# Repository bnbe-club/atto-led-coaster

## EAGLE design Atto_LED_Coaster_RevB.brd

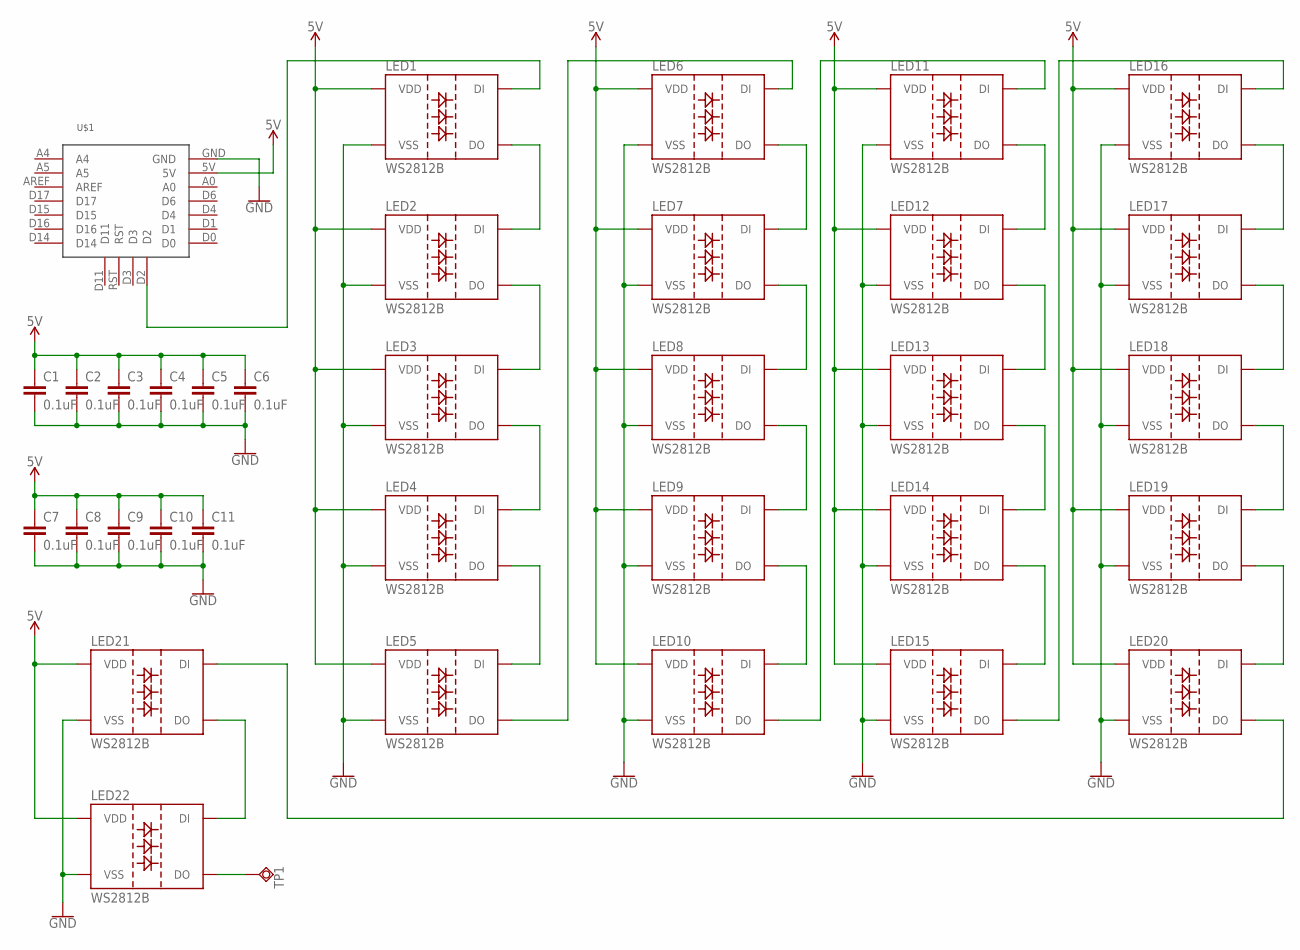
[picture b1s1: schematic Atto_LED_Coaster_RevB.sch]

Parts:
C1, C2, C3, C4, C5, C6, C7, C8, C9, C10, C11: 0.1uF; C0805
LED1, LED2, LED3, LED4, LED5, LED6, LED7, LED8, LED9, LED10, LED11, LED12, LED13, LED14, LED15, LED16, LED17, LED18, LED19, LED20, LED21, LED22: WS2812B
TP1: TPSQTP20R; TP20R
U$1: PIKSEY_ATTO

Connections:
5V: C1.1, C2.1, C3.1, C4.1, C5.1, C6.1, C7.1, C8.1, C9.1, C10.1, C11.1, LED1.3 (VDD), LED2.3 (VDD), LED3.3 (VDD), LED4.3 (VDD), LED5.3 (VDD), LED6.3 (VDD), LED7.3 (VDD), LED8.3 (VDD), LED9.3 (VDD), LED10.3 (VDD), LED11.3 (VDD), LED12.3 (VDD), LED13.3 (VDD), LED14.3 (VDD), LED15.3 (VDD), LED16.3 (VDD), LED17.3 (VDD), LED18.3 (VDD), LED19.3 (VDD), LED20.3 (VDD), LED21.3 (VDD), LED22.3 (VDD), U$1.5V
GND: C1.2, C2.2, C3.2, C4.2, C5.2, C6.2, C7.2, C8.2, C9.2, C10.2, C11.2, LED1.1 (VSS), LED2.1 (VSS), LED3.1 (VSS), LED4.1 (VSS), LED5.1 (VSS), LED6.1 (VSS), LED7.1 (VSS), LED8.1 (VSS), LED9.1 (VSS), LED10.1 (VSS), LED11.1 (VSS), LED12.1 (VSS), LED13.1 (VSS), LED14.1 (VSS), LED15.1 (VSS), LED16.1 (VSS), LED17.1 (VSS), LED18.1 (VSS), LED19.1 (VSS), LED20.1 (VSS), LED21.1 (VSS), LED22.1 (VSS), U$1.GND
unnamed: LED1.2 (DO), LED2.4 (DI)
unnamed: LED2.2 (DO), LED3.4 (DI)
unnamed: LED3.2 (DO), LED4.4 (DI)
unnamed: LED4.2 (DO), LED5.4 (DI)
unnamed: LED6.2 (DO), LED7.4 (DI)
unnamed: LED7.2 (DO), LED8.4 (DI)
unnamed: LED8.2 (DO), LED9.4 (DI)
unnamed: LED9.2 (DO), LED10.4 (DI)
unnamed: LED11.2 (DO), LED12.4 (DI)
unnamed: LED12.2 (DO), LED13.4 (DI)
unnamed: LED13.2 (DO), LED14.4 (DI)
unnamed: LED14.2 (DO), LED15.4 (DI)
unnamed: LED16.2 (DO), LED17.4 (DI)
unnamed: LED17.2 (DO), LED18.4 (DI)
unnamed: LED18.2 (DO), LED19.4 (DI)
unnamed: LED19.2 (DO), LED20.4 (DI)
unnamed: LED22.2 (DO), TP1.TP
unnamed: LED15.2 (DO), LED16.4 (DI)
unnamed: LED10.2 (DO), LED11.4 (DI)
unnamed: LED5.2 (DO), LED6.4 (DI)
unnamed: LED1.4 (DI), U$1.D2
unnamed: LED21.2 (DO), LED22.4 (DI)
unnamed: LED20.2 (DO), LED21.4 (DI)

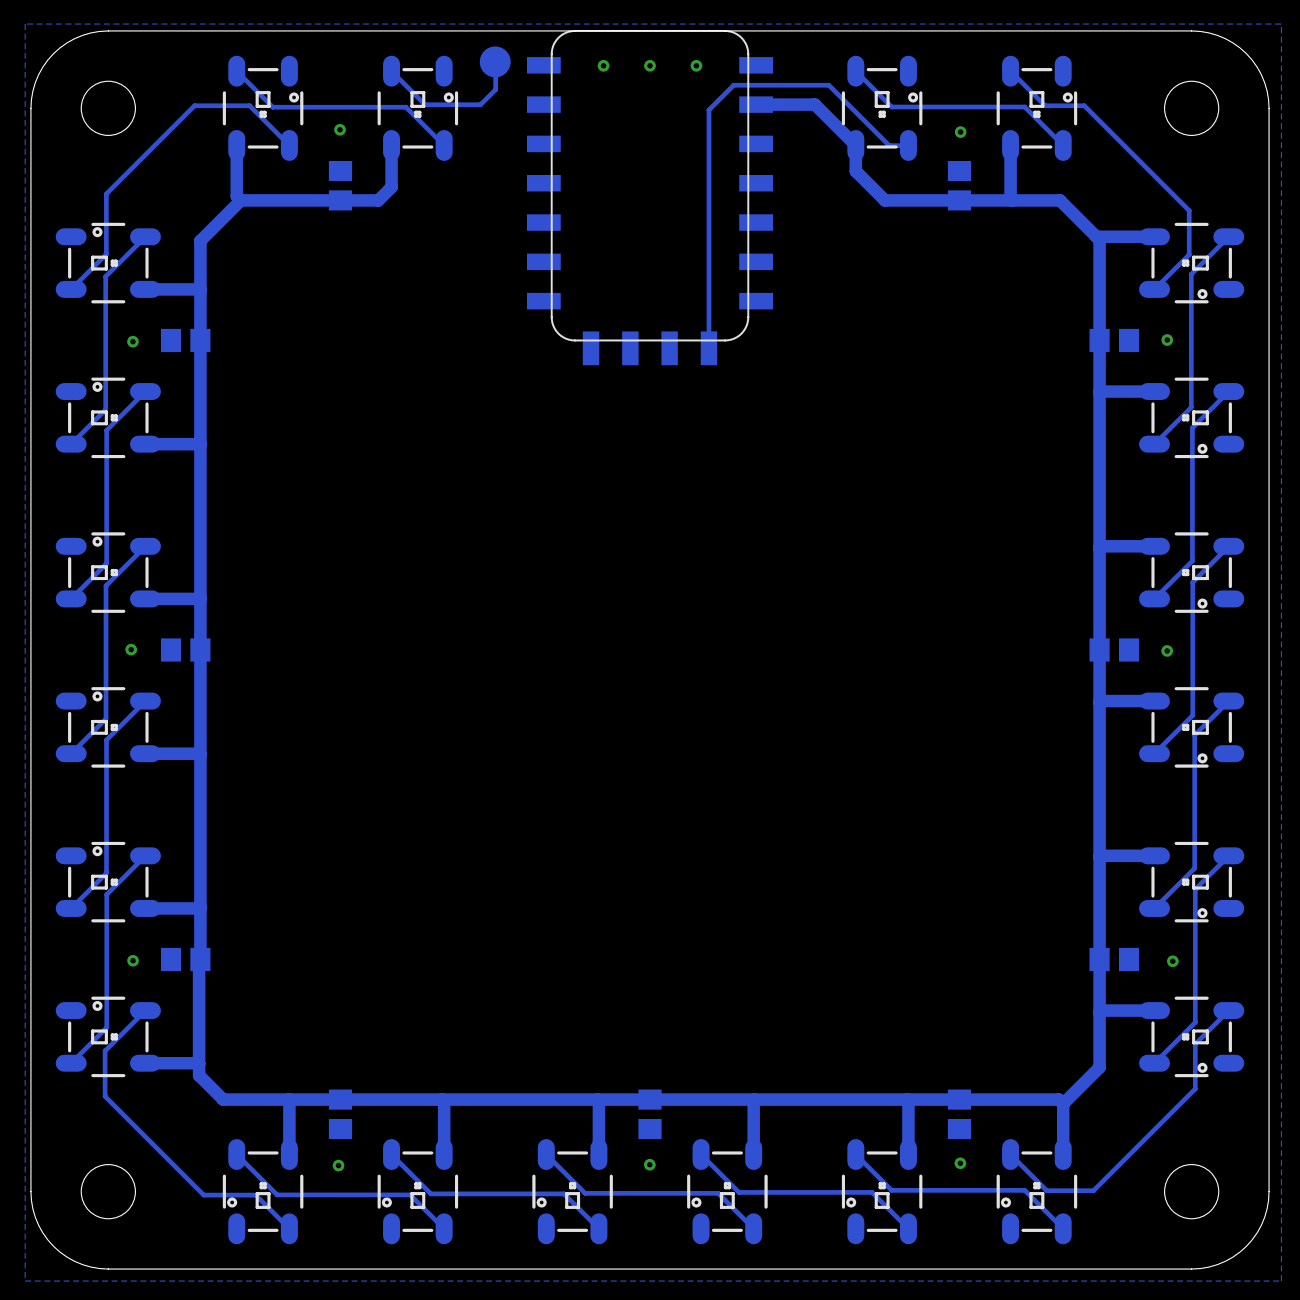
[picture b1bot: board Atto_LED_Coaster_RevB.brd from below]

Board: 2 copper layers, 80.0 x 80.0 mm, 35 parts (35 on the bottom side), 25 nets.

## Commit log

2020-01-08 Initial release

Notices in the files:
parts and their libraries:
SparkFun-PowerSymbols: Licensing: Creative Commons ShareAlike 4.0 International - https://creativecommons.org/licenses/by-sa/4.0
